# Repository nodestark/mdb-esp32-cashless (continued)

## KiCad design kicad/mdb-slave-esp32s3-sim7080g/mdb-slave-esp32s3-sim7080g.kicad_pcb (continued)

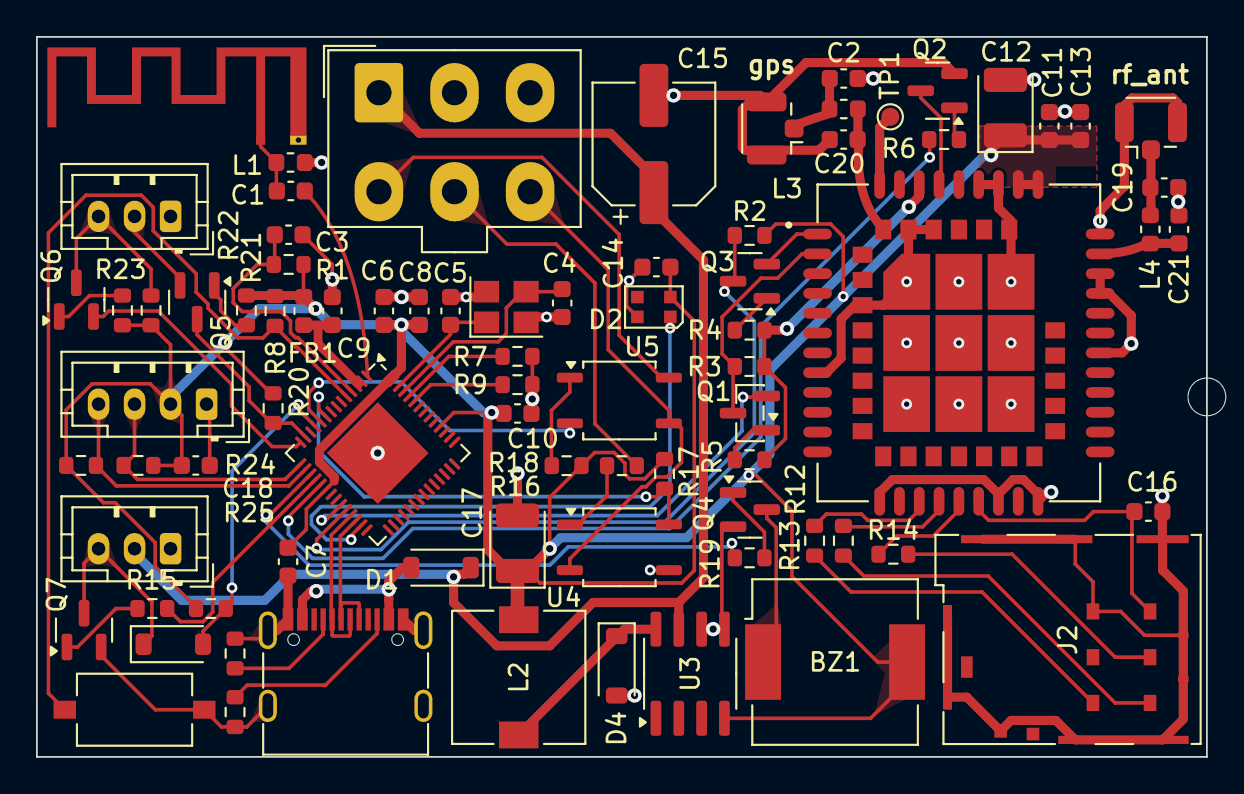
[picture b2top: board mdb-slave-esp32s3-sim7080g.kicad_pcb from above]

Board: 2 copper layers, 65.0 x 40.0 mm, 82 parts (0 on the bottom side), 63 nets.

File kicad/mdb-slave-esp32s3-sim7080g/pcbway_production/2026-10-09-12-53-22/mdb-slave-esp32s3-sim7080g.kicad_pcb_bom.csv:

Designator,Quantity,Value,Footprint,Package,MPN,DNP,Mount_Type,Description,LCSC#,MF,MAXIMUM_PACKAGE_HEIGHT,Price,Check_prices,STANDARD,PARTREV,SnapEDA_Link,MP,Description_1,Availability,MANUFACTURER
BZ1,1,Buzzer,Buzzer_CUI_CPT-9019S-SMT,,,,smt,"Buzzer, polarized",C255327,,,,,,,,,,,
"C1, C19, C2",3,1.8pf,C_0603_1608Metric,,,,smt,,C376773,,,,,,,,,,,
"C10, C11, C14, C16, C18, C7, C9",7,0.1uF,C_0603_1608Metric,,,,smt,,C5137636,,,,,,,,,,,
C12,1,10uF,CP_EIA-3528-21_Kemet-B,,,,smt,Polarized capacitor,C110053,,,,,,,,,,,
"C13, C3, C8",3,1uF,C_0603_1608Metric,,,,smt,,C6119849,,,,,,,,,,,
C15,1,100uF,CP_Elec_6.3x5.8,,,,smt,Polarized capacitor,C128464,,,,,,,,,,,
C17,1,220uF,CP_EIA-3528-21_Kemet-B,,,,smt,Polarized capacitor,C30242,,,,,,,,,,,
"C4, C5",2,12pF,C_0603_1608Metric,,,,smt,,C363546,,,,,,,,,,,
C6,1,10uF,C_0603_1608Metric,,,,smt,,C6119864,,,,,,,,,,,
"D1, D3, D4",3,D_Schottky,D_SOD-123,,,,smt,Schottky diode,C18195164,,,,,,,,,,,
D2,1,XL-2121RGBC-2812B,LED_WS2812B-2020_PLCC4_2.0x2.0mm,,,,smt,"RGB LED with integrated controller, 2.0 x 2.0 mm, 12 mA",C5349957,,,,,,,,,,,
FB1,1,FerriteBead_Small,L_0603_1608Metric,,,,smt,"Ferrite bead, small symbol",C14709,,,,,,,,,,,
J1,1,USB_C_Receptacle_USB2.0_16P,USB_C_Receptacle_G-Switch_GT-USB-7010ASV,,,,smt,USB 2.0-only 16P Type-C Receptacle connector,C2988369,,,,,,,,,,,
J2,1,JAE_SIM_Card_SF72S006,JAE_SIM_Card_SF72S006,,,,smt,Nano-SIM Card (4FF) connector with Detect Switch,C2977286,,,,,,,,,,,
"J3, J7",2,Conn_01x03_Pin,JST_PH_B3B-PH-K_1x03_P2.00mm_Vertical,,,,tht,"Generic connector, single row, 01x03, script generated",C131339,,,,,,,,,,,
"J4, J5",2,Conn_Coaxial,U.FL_Hirose_U.FL-R-SMT-1_Vertical,,,,smt,"coaxial connector (BNC, SMA, SMB, SMC, Cinch/RCA, LEMO, ...)",C88374,,,,,,,,,,,
J6,1,MDB_Connector,Molex_Mini-Fit_Jr_5566-06A_2x03_P4.20mm_Vertical,,,,tht,"Generic connector, double row, 02x03, top/bottom pin numbering scheme (row 1: 1...pins_per_row, row2: pins_per_row+1 ... num_pins), script generated (kicad-library-utils/schlib/autogen/connector/)",C22365701,,,,,,,,,,,
J8,1,Conn_01x04_Pin,JST_PH_B4B-PH-K_1x04_P2.00mm_Vertical,,,,tht,"Generic connector, single row, 01x04, script generated",C131334,,,,,,,,,,,
L1,1,2.4nh,L_0603_1608Metric,,,,smt,,C2042508,,,,,,,,,,,
L2,1,100uH,L_7.3x7.3_H3.5,,,,smt,Inductor,C182195,,,,,,,,,,,
L3,1,5.6nh,L_0603_1608Metric,,,,smt,,C6652920,,,,,,,,,,,
L4,1,3.9nh,L_0603_1608Metric,,,,smt,,C317982,,,,,,,,,,,
"Q1, Q2, Q3, Q4, Q5, Q6, Q7",7,MMBT3904,SOT-23,,,,smt,"0.2A Ic, 40V Vce, Small Signal NPN Transistor, SOT-23",C916374,,,,,,,,,,,
"R1, R2, R20, R22, R27, R3, R7, R8, R9",9,10k,R_0603_1608Metric,,,,smt,,C98220,,,,,,,,,,,
"R10, R11",2,5.1k,R_0603_1608Metric,,,,smt,,C394543,,,,,,,,,,,
"R12, R13, R14",3,22ohm,R_0603_1608Metric,,,,smt,,C23345,,,,,,,,,,,
"R15, R19, R21, R23, R24, R25, R4, R5, R6",9,4K7,R_0603_1608Metric,,,,smt,,C23162,,,,,,,,,,,
R16,1,470ohm,R_0603_1608Metric,,,,smt,Resistor,C114669,,,,,,,,,,,
R18,1,100ohm,R_0603_1608Metric,,,,smt,Resistor,C22775,,,,,,,,,,,
R17,1,1k,R_0603_1608Metric,,,,smt,,C2907113,,,,,,,,,,,
SW1,1,SW_Push,SW_Tactile_SPST_NO_Straight_CK_PTS636Sx25SMTRLFS,,,,smt,,C42435421,,,,,,,,,,,
U1,1,ESP32-S3FH4R2,QFN-56-1EP_7x7mm_P0.4mm_EP4x4mm,,,,smt,,C3013940,,,,,,,,,,,
U2,1,SIM7080G,XCVR_SIM7080G,Package,,,smt,,C2943992,SIMCom,2.6 mm,None,https://www.snapeda.com/parts/SIM7080G/SIMCom/view-part/?ref=eda,Manufacturer Recommendation,1.04,https://www.snapeda.com/parts/SIM7080G/SIMCom/view-part/?ref=snap,SIM7080G,"Cellular, Navigation Galileo, GLONASS, GPS, GNSS, LTE Transceiver Module 1.559GHz ~ 1.576GHz, 1.575GHz ~ 1.576GHz, 1.574GHz ~ 1.606GHz, 1.598GHz ~ 1.563GHz Antenna Not Included Surface Mount",In Stock,SIMCOM
U3,1,LM2594HVM-3.3,SOIC-8_3.9x4.9mm_P1.27mm,,,,smt,"3.3V, 0.5A SIMPLE SWITCHER® Step-Down Voltage Regulator, Maximum VIN 60V, SOIC-8",C18057294,,,,,,,,,,,
"U4, U5",2,TLP785,SOP-4_3.8x4.1mm_P2.54mm,,,,smt,"DC Optocoupler, Vce 80V, CTR 50-200%, DIP4",C128776,,,,,,,,,,,
Y1,1,Crystal_GND24,Crystal_SMD_3225-4Pin_3.2x2.5mm,,,,smt,"Four pin crystal, GND on pins 2 and 4",C7294599,,,,,,,,,,,

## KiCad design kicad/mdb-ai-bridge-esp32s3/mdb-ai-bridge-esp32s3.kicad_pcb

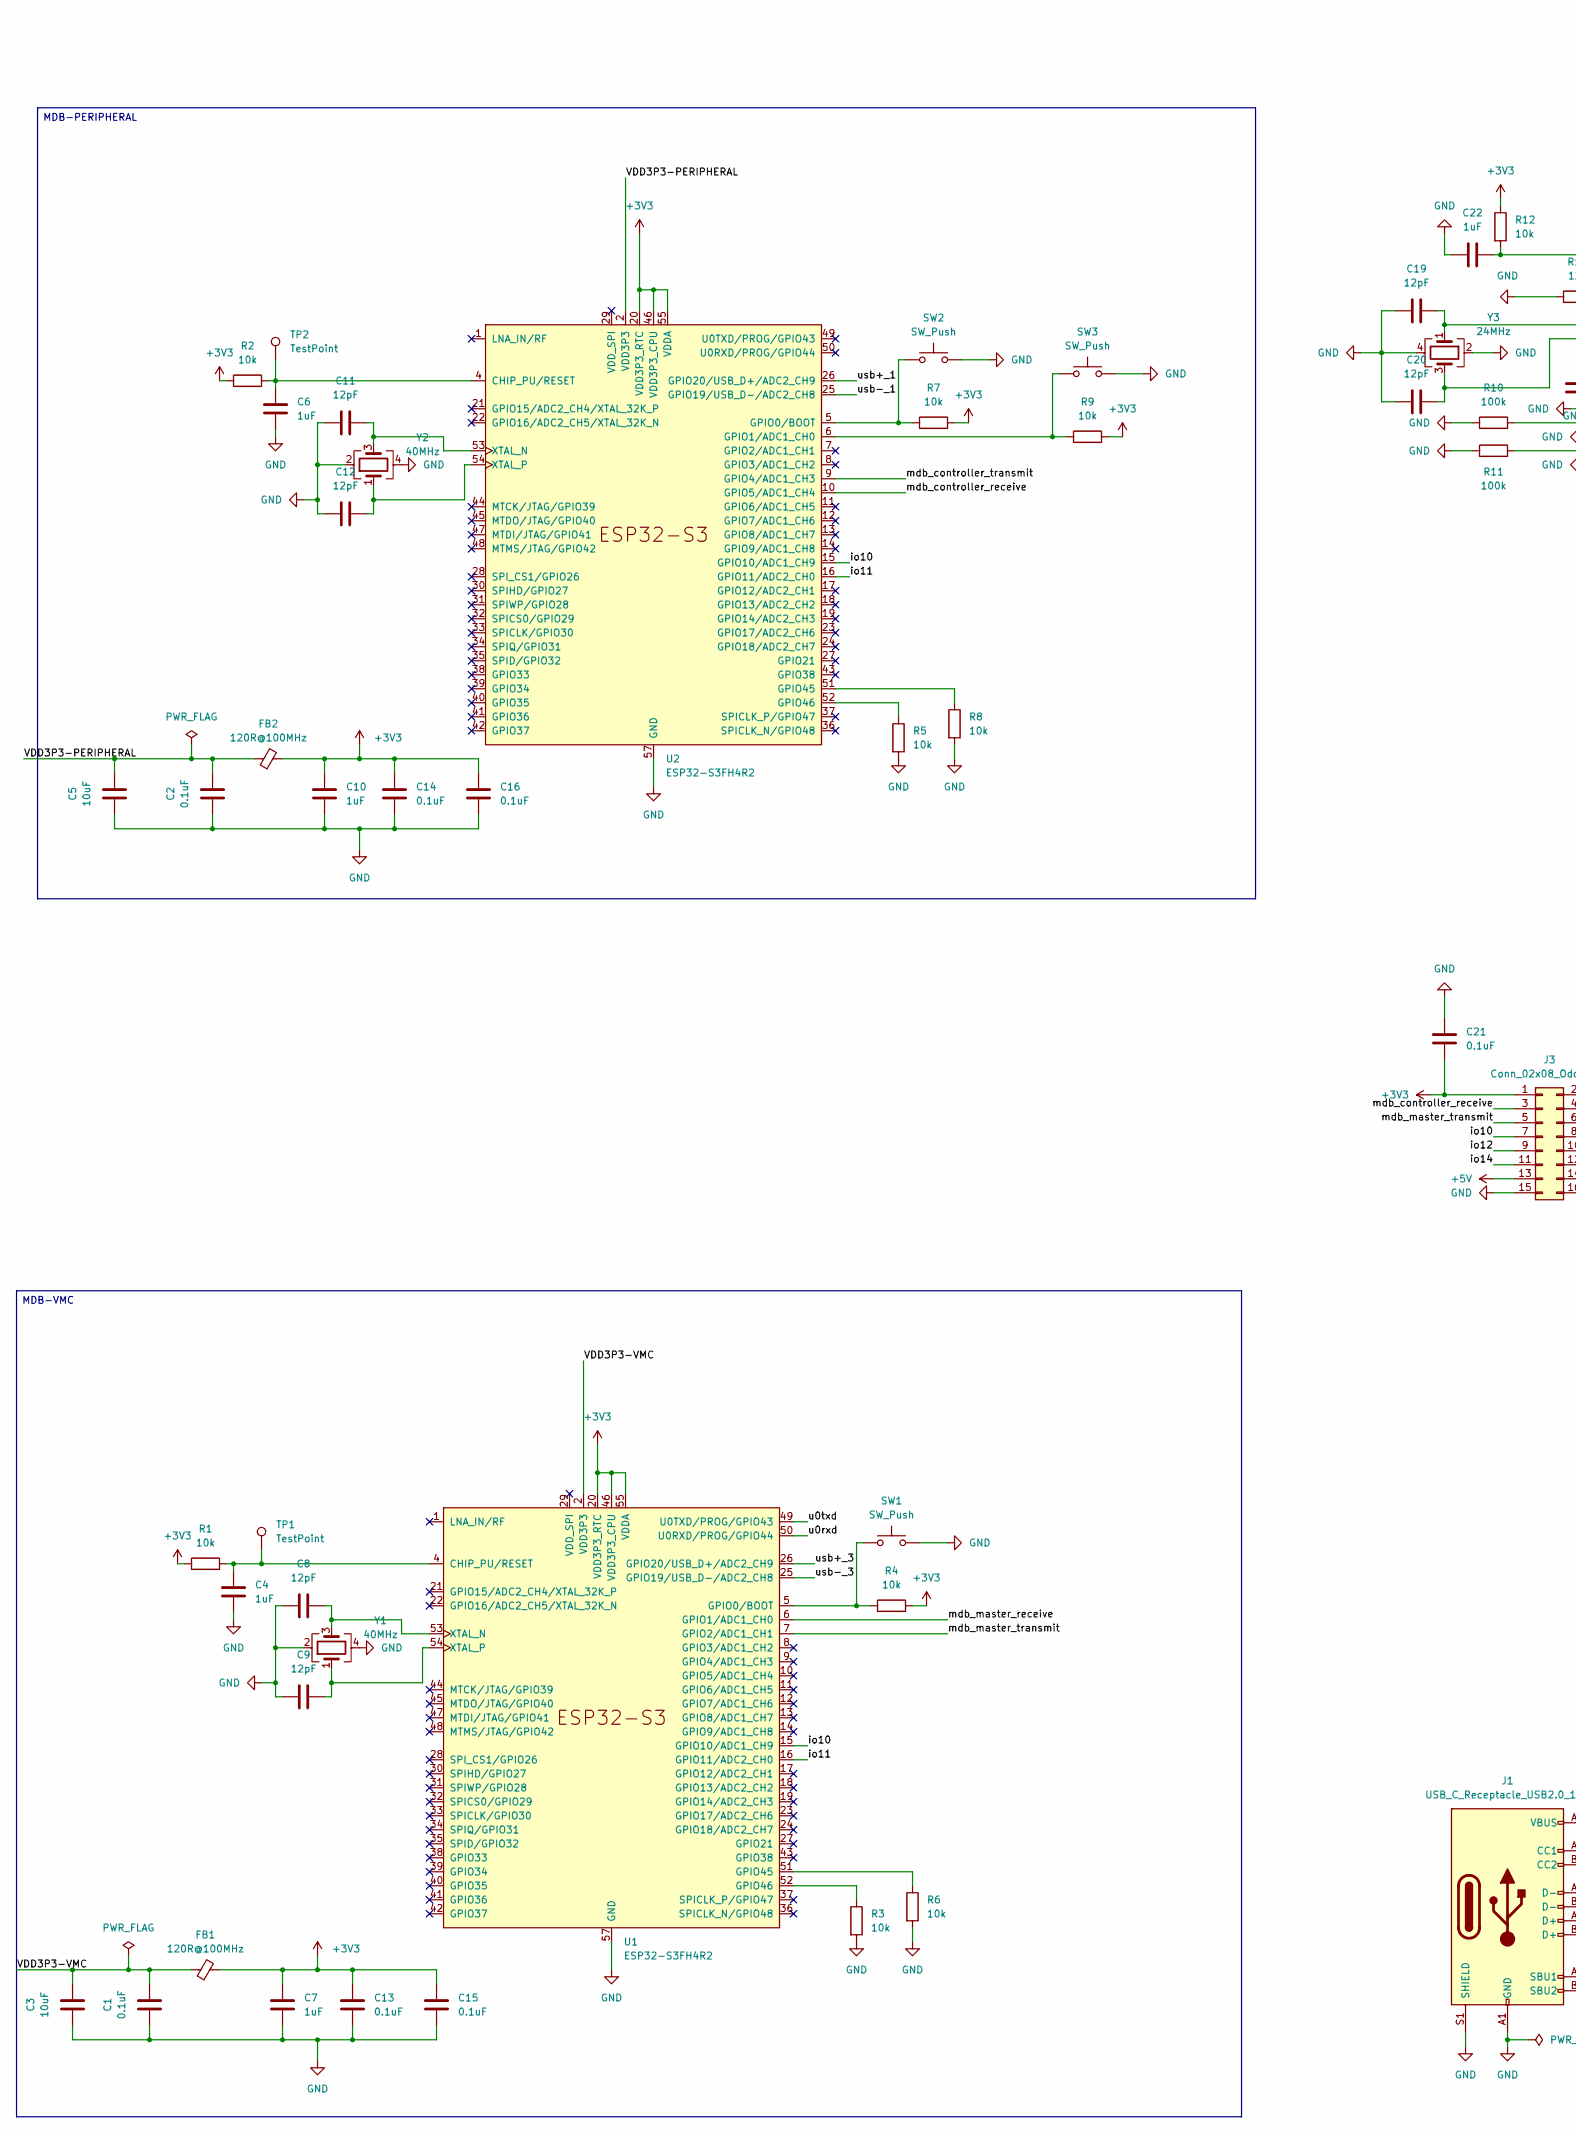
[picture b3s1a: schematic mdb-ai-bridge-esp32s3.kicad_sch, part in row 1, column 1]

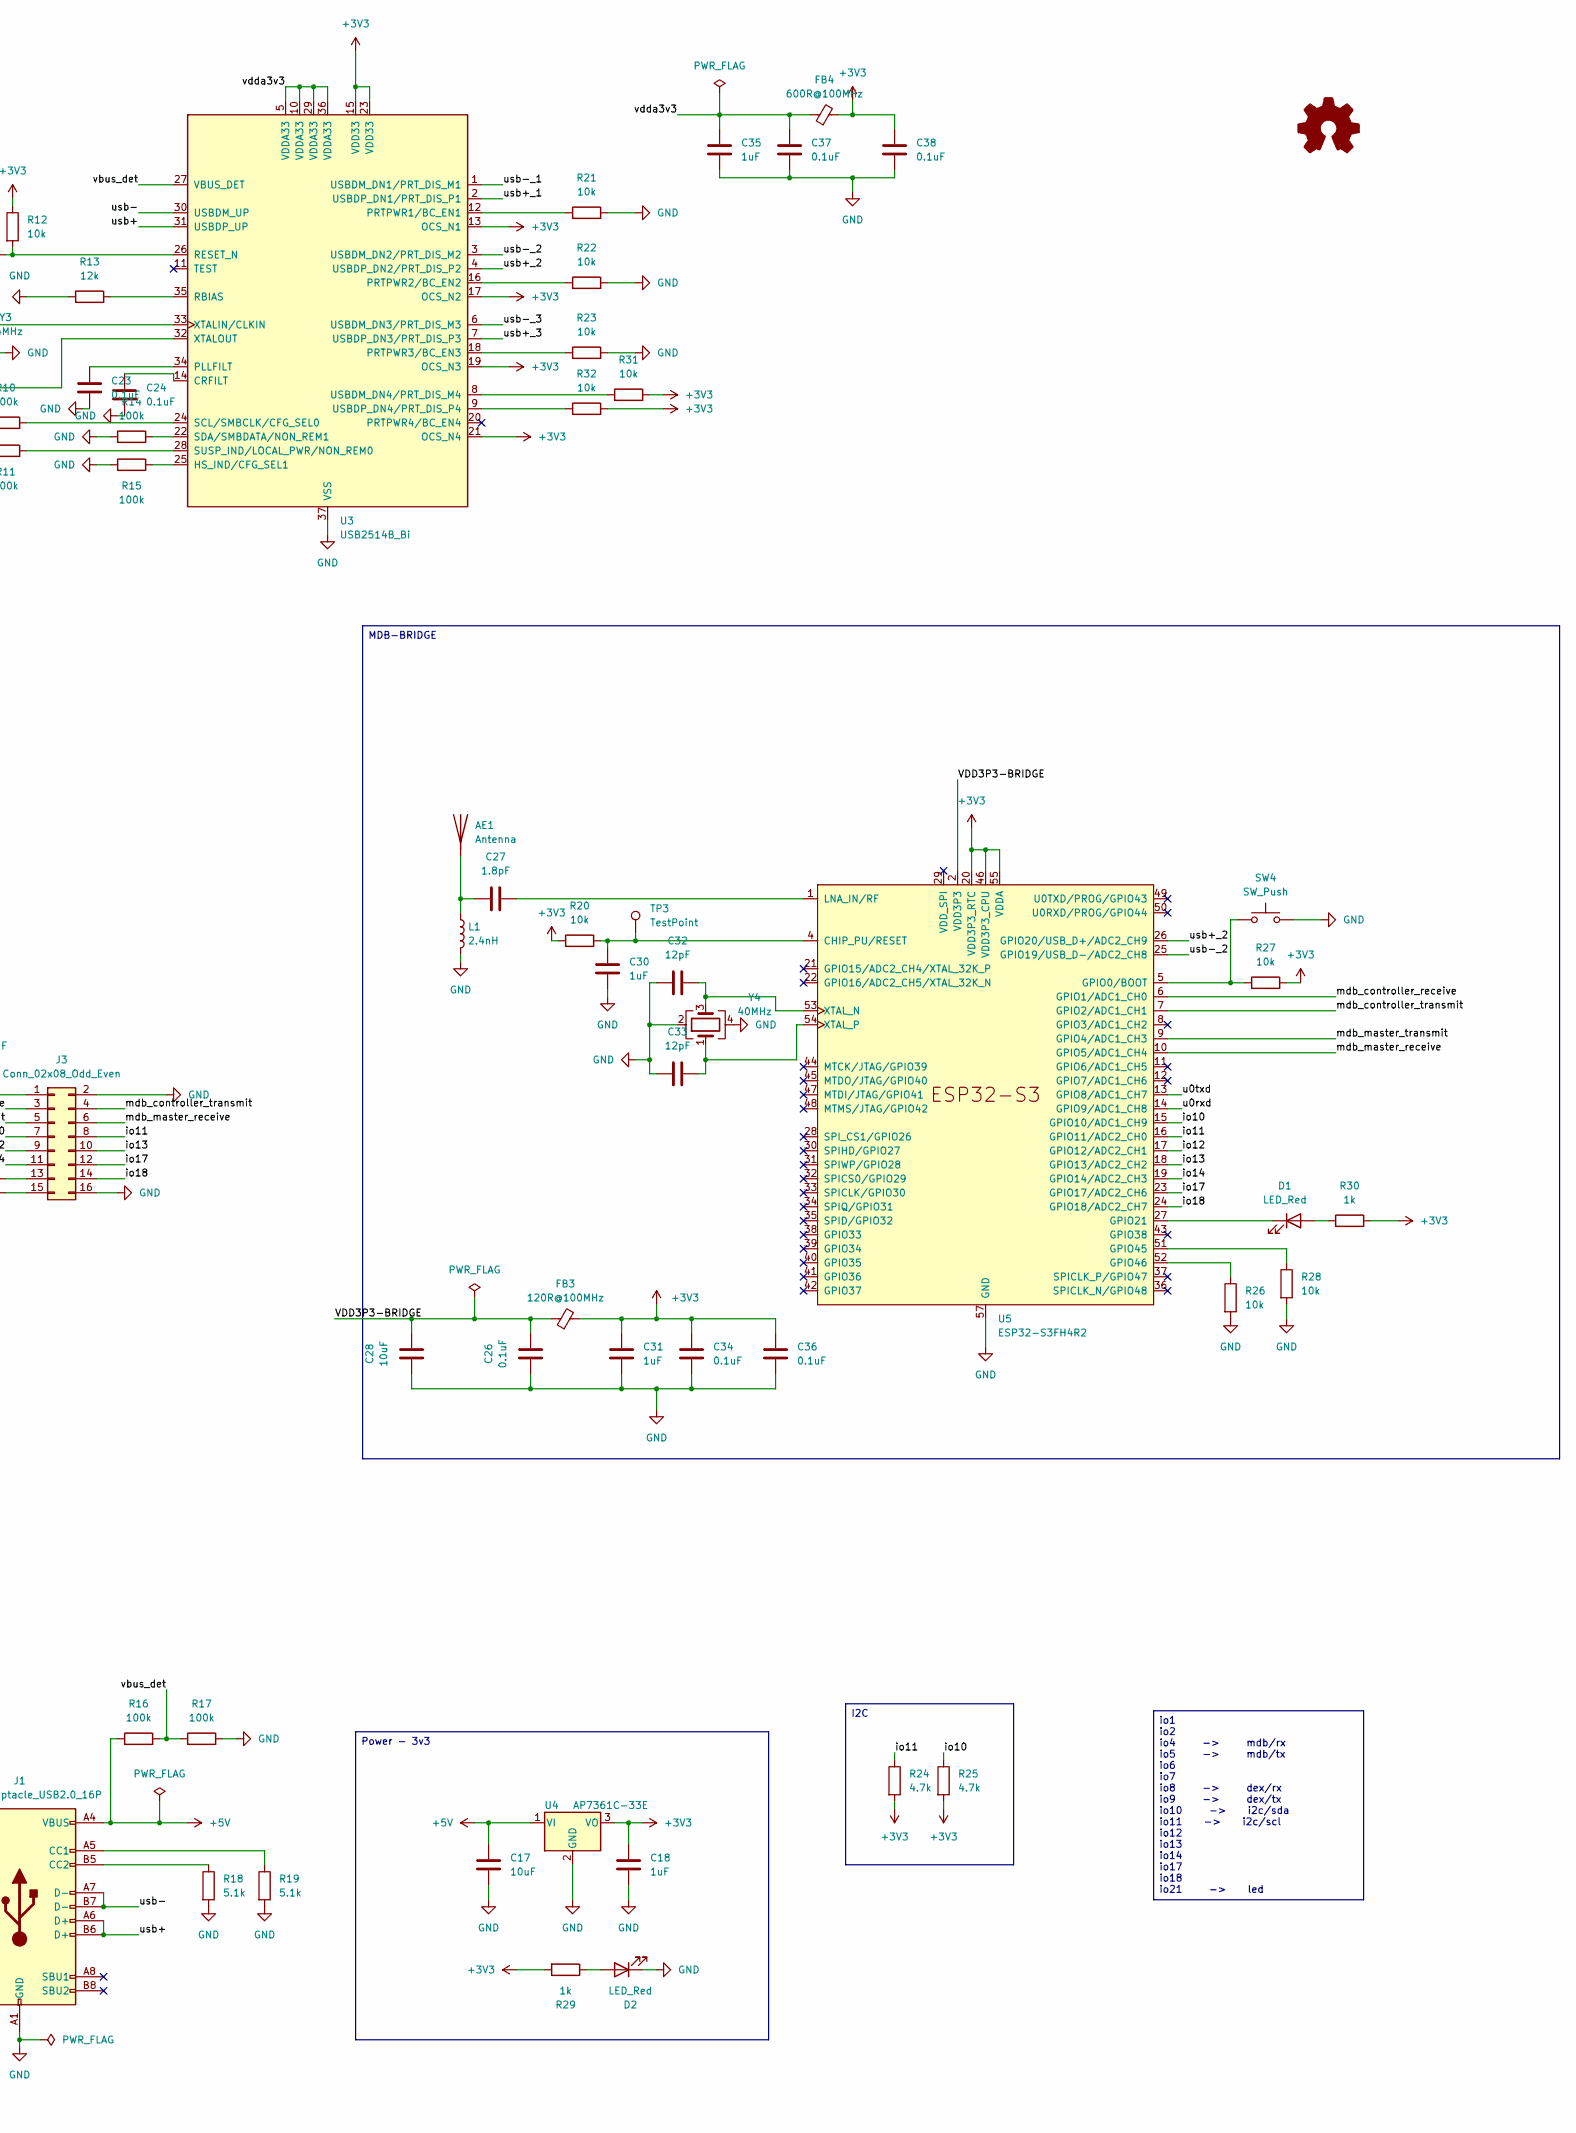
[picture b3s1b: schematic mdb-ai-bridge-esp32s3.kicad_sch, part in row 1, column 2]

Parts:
AE1: Antenna; Texas_SWRA117D_2.4GHz_Left
C1, C2, C13, C14, C15, C16, C21, C23, C24, C26, C34, C36, C37, C38: 0.1uF; C_0402_1005Metric; LCSC# C1525
C3, C5, C28: 10uF; C_0402_1005Metric; LCSC# C15525
C4, C6, C7, C10, C18, C22, C30, C31, C35: 1uF; C_0402_1005Metric; LCSC# C52923
C8, C9, C11, C12, C19, C20, C32, C33: 12pF; C_0402_1005Metric; LCSC# C1547
C17: 10uF; C_0402_1005Metric; LCSC# C7472949
C27: 1.8pF; C_0402_1005Metric; LCSC# C76902
D1, D2: LED_Red; LED_0402_1005Metric; LCSC# C779449
FB1, FB2, FB3: 120R@100MHz; L_0402_1005Metric; LCSC# C88970
FB4: 600R@100MHz; L_0402_1005Metric; LCSC# C160977
J1: USB_C_Receptacle_USB2.0_16P; USB_C_Receptacle_G-Switch_GT-USB-7010ASV; LCSC# C2988369
J3: Conn_02x08_Odd_Even; PinHeader_2x08_P2.54mm_Vertical
L1: 2.4nH; L_0402_1005Metric; LCSC# C167473
R1, R2, R3, R4, R5, R6, R7, R8, R9, R12, R20, R21, R22, R23, R26, R27, R28, R31, R32: 10k; R_0402_1005Metric; LCSC# C25744
R10, R11, R14, R15, R16, R17: 100k; R_0402_1005Metric; LCSC# C25741
R13: 12k; R_0402_1005Metric; LCSC# C25752
R18, R19: 5.1k; R_0402_1005Metric; LCSC# C25905
R24, R25: 4.7k; R_0402_1005Metric; LCSC# C25900
R29, R30: 1k; R_0402_1005Metric; LCSC# C11702
SW1, SW2, SW3, SW4: SW_Push; SW_Tactile_SPST_NO_Straight_CK_PTS636Sx25SMTRLFS; LCSC# C42435421
TP1, TP2, TP3: TestPoint; TestPoint_Pad_D1.5mm
U1, U2, U5: ESP32-S3FH4R2; QFN-56-1EP_7x7mm_P0.4mm_EP4x4mm; LCSC# C3013940
U3: USB2514B_Bi; QFN-36-1EP_6x6mm_P0.5mm_EP3.7x3.7mm; LCSC# C510949
U4: AP7361C-33E; SOT-223-3_TabPin2; LCSC# C500795
Y1, Y2, Y4: 40MHz; Crystal_SMD_3225-4Pin_3.2x2.5mm; LCSC# C7294599
Y3: 24MHz; Crystal_SMD_3225-4Pin_3.2x2.5mm; LCSC# C70583

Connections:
+3V3: C7.2, C10.2, C13.1, C14.1, C15.1, C16.1, C18.2, C21.1, C31.2, C34.1, C36.1, C38.1, FB1.2, FB2.2, FB3.2, FB4.2, J3.1, R1.1, R2.1, R4.2, R7.2, R9.2, R12.1, R20.1, R24.2, R25.2, R27.2, R29.2, R30.2, R31.2, R32.2, U1.20 (VDD3P3_RTC), U1.46 (VDD3P3_CPU), U1.55 (VDDA), U1.56 (VDDA), U2.20 (VDD3P3_RTC), U2.46 (VDD3P3_CPU), U2.55 (VDDA), U2.56 (VDDA), U3.13 (OCS_N1), U3.15 (VDD33), U3.17 (OCS_N2), U3.19 (OCS_N3), U3.21 (OCS_N4), U3.23 (VDD33), U4.3 (VO), U5.20 (VDD3P3_RTC), U5.46 (VDD3P3_CPU), U5.55 (VDDA), U5.56 (VDDA)
+5V: C17.2, J1.A4 (VBUS), J1.A9 (VBUS), J1.B4 (VBUS), J1.B9 (VBUS), J3.13, R16.1, U4.1 (VI)
/VDD3P3-BRIDGE: C26.2, C28.2, FB3.1, U5.2 (VDD3P3), U5.3 (VDD3P3)
/VDD3P3-PERIPHERAL: C2.2, C5.2, FB2.1, U2.2 (VDD3P3), U2.3 (VDD3P3)
/VDD3P3-VMC: C1.2, C3.2, FB1.1, U1.2 (VDD3P3), U1.3 (VDD3P3)
/io10: J3.7, R25.1, U1.15 (GPIO10/ADC1_CH9), U2.15 (GPIO10/ADC1_CH9), U5.15 (GPIO10/ADC1_CH9)
/io11: J3.8, R24.1, U1.16 (GPIO11/ADC2_CH0), U2.16 (GPIO11/ADC2_CH0), U5.16 (GPIO11/ADC2_CH0)
/io12: J3.9, U5.17 (GPIO12/ADC2_CH1)
/io13: J3.10, U5.18 (GPIO13/ADC2_CH2)
/io14: J3.11, U5.19 (GPIO14/ADC2_CH3)
/io17: J3.12, U5.23 (GPIO17/ADC2_CH6)
/io18: J3.14, U5.24 (GPIO18/ADC2_CH7)
/mdb_controller_receive: J3.3, U2.10 (GPIO5/ADC1_CH4), U5.6 (GPIO1/ADC1_CH0)
/mdb_controller_transmit: J3.4, U2.9 (GPIO4/ADC1_CH3), U5.7 (GPIO2/ADC1_CH1)
/mdb_master_receive: J3.6, U1.6 (GPIO1/ADC1_CH0), U5.10 (GPIO5/ADC1_CH4)
/mdb_master_transmit: J3.5, U1.7 (GPIO2/ADC1_CH1), U5.9 (GPIO4/ADC1_CH3)
/u0rxd: U1.50 (U0RXD/PROG/GPIO44), U5.14 (GPIO9/ADC1_CH8)
/u0txd: U1.49 (U0TXD/PROG/GPIO43), U5.13 (GPIO8/ADC1_CH7)
/usb+: J1.A6 (D+), J1.B6 (D+), U3.31 (USBDP_UP)
/usb+_1: U2.26 (GPIO20/USB_D+/ADC2_CH9), U3.2 (USBDP_DN1/PRT_DIS_P1)
/usb+_2: U3.4 (USBDP_DN2/PRT_DIS_P2), U5.26 (GPIO20/USB_D+/ADC2_CH9)
/usb+_3: U1.26 (GPIO20/USB_D+/ADC2_CH9), U3.7 (USBDP_DN3/PRT_DIS_P3)
/usb-: J1.A7 (D-), J1.B7 (D-), U3.30 (USBDM_UP)
/usb-_1: U2.25 (GPIO19/USB_D-/ADC2_CH8), U3.1 (USBDM_DN1/PRT_DIS_M1)
/usb-_2: U3.3 (USBDM_DN2/PRT_DIS_M2), U5.25 (GPIO19/USB_D-/ADC2_CH8)
/usb-_3: U1.25 (GPIO19/USB_D-/ADC2_CH8), U3.6 (USBDM_DN3/PRT_DIS_M3)
/vbus_det: R16.2, R17.1, U3.27 (VBUS_DET)
/vdda3v3: C35.2, C37.1, FB4.1, U3.5 (VDDA33), U3.10 (VDDA33), U3.29 (VDDA33), U3.36 (VDDA33)
GND: C1.1, C2.1, C3.1, C4.2, C5.1, C6.2, C7.1, C8.1, C9.1, C10.1, C11.1, C12.1, C13.2, C14.2, C15.2, C16.2, C17.1, C18.1, C19.1, C20.1, C21.2, C22.2, C23.1, C24.1, C26.1, C28.1, C30.2, C31.1, C32.1, C33.1, C34.2, C35.1, C36.2, C37.2, C38.2, D2.1 (K), J1.A1 (GND), J1.A12 (GND), J1.B1 (GND), J1.B12 (GND), J1.S1 (SHIELD), J3.2, J3.15, J3.16, L1.2, R3.2, R5.2, R6.2, R8.2, R10.1, R11.1, R13.1, R14.1, R15.1, R17.2, R18.2, R19.2, R21.2, R22.2, R23.2, R26.2, R28.2, SW1.2, SW2.2, SW3.2, SW4.2, U1.57 (GND), U2.57 (GND), U3.37 (VSS), U4.2 (GND), U5.57 (GND), Y1.2, Y1.4, Y2.2, Y2.4, Y3.2, Y3.4, Y4.2, Y4.4
unnamed: AE1.1 (A), C27.1, L1.1
unnamed: D1.2 (A), R30.1
unnamed: D1.1 (K), U5.27 (GPIO21)
unnamed: D2.2 (A), R29.1
unnamed: J1.A5 (CC1), R19.1
unnamed: J1.B5 (CC2), R18.1
unnamed: C4.1, R1.2, TP1.1, U1.4 (CHIP_PU/RESET)
unnamed: R4.1, SW1.1, U1.5 (GPIO0/BOOT)
unnamed: R6.1, U1.51 (GPIO45)
unnamed: R3.1, U1.52 (GPIO46)
unnamed: C8.2, U1.53 (XTAL_N), Y1.3
unnamed: C9.2, U1.54 (XTAL_P), Y1.1
unnamed: C6.1, R2.2, TP2.1, U2.4 (CHIP_PU/RESET)
unnamed: R7.1, SW2.1, U2.5 (GPIO0/BOOT)
unnamed: R9.1, SW3.1, U2.6 (GPIO1/ADC1_CH0)
unnamed: R8.1, U2.51 (GPIO45)
unnamed: R5.1, U2.52 (GPIO46)
unnamed: C11.2, U2.53 (XTAL_N), Y2.3
unnamed: C12.2, U2.54 (XTAL_P), Y2.1
unnamed: C24.2, U3.14 (CRFILT)
unnamed: R15.2, U3.25 (HS_IND/CFG_SEL1)
unnamed: C23.2, U3.34 (PLLFILT)
unnamed: R21.1, U3.12 (PRTPWR1/BC_EN1)
unnamed: R22.1, U3.16 (PRTPWR2/BC_EN2)
unnamed: R23.1, U3.18 (PRTPWR3/BC_EN3)
unnamed: R13.2, U3.35 (RBIAS)
unnamed: C22.1, R12.2, U3.26 (RESET_N)
unnamed: R10.2, U3.24 (SCL/SMBCLK/CFG_SEL0)
unnamed: R14.2, U3.22 (SDA/SMBDATA/NON_REM1)
unnamed: R11.2, U3.28 (SUSP_IND/LOCAL_PWR/NON_REM0)
unnamed: R31.1, U3.8 (USBDM_DN4/PRT_DIS_M4)
unnamed: R32.1, U3.9 (USBDP_DN4/PRT_DIS_P4)
unnamed: C19.2, U3.33 (XTALIN/CLKIN), Y3.1
unnamed: C20.2, U3.32 (XTALOUT), Y3.3
unnamed: C30.1, R20.2, TP3.1, U5.4 (CHIP_PU/RESET)
unnamed: R27.1, SW4.1, U5.5 (GPIO0/BOOT)
unnamed: R28.1, U5.51 (GPIO45)
unnamed: R26.1, U5.52 (GPIO46)
unnamed: C27.2, U5.1 (LNA_IN/RF)
unnamed: C32.2, U5.53 (XTAL_N), Y4.3
unnamed: C33.2, U5.54 (XTAL_P), Y4.1

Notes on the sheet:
MDB-PERIPHERAL
Power - 3v3
MDB-BRIDGE
MDB-VMC
io1 io2 io4 -> mdb/rx io5 -> mdb/tx io6 io7 io8 -> dex/rx io9 -> dex/tx io10 -> i2c/sda io11 -> i2c/scl io12 io13 io14 io17 io18 io21 -> led
I2C

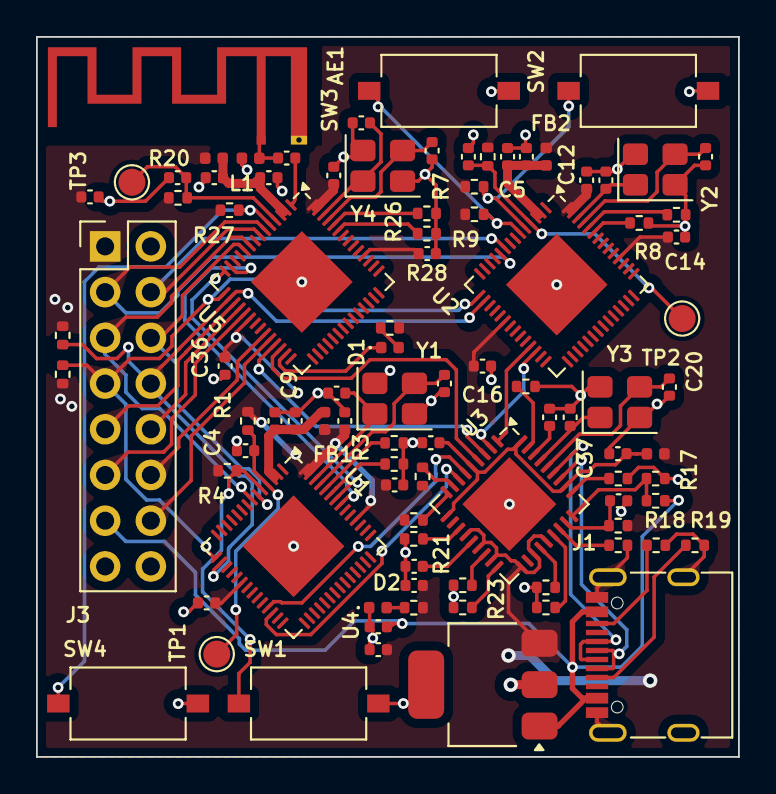
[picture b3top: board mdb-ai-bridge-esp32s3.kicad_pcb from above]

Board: 2 copper layers, 39.0 x 40.0 mm, 94 parts (0 on the bottom side), 70 nets.

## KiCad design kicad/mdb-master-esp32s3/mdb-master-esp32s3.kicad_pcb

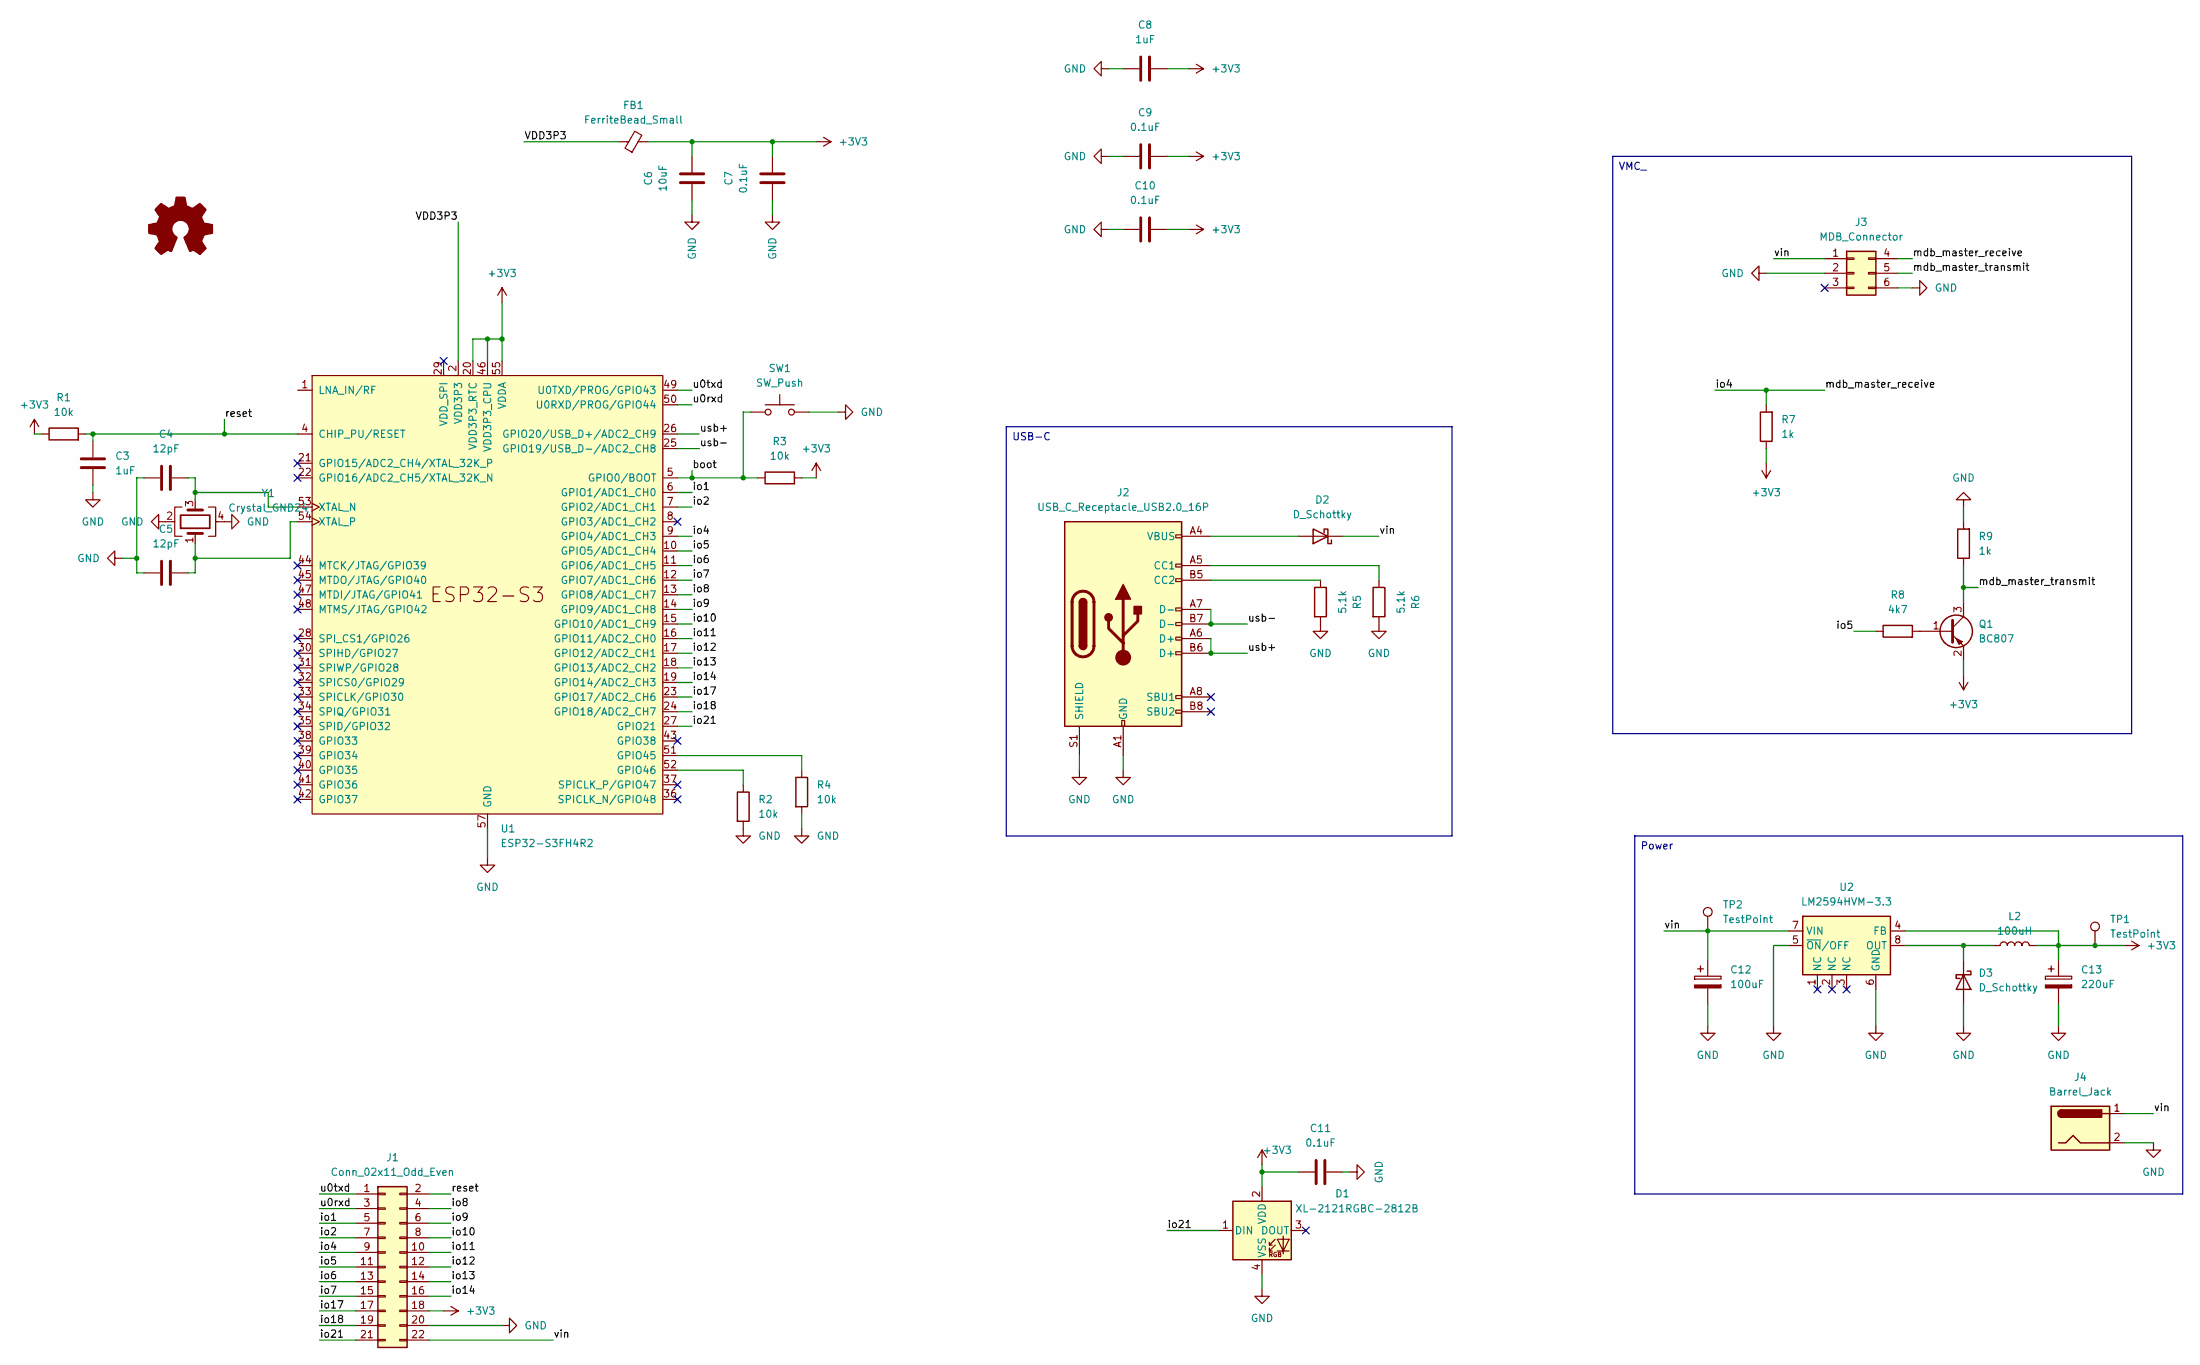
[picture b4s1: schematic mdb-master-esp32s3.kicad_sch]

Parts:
C3, C8: 1uF; C_0603_1608Metric; LCSC# C6119849
C4, C5: 12pF; C_0603_1608Metric; LCSC# C363546
C6: 10uF; C_0603_1608Metric; LCSC# C6119864
C7, C9, C10, C11: 0.1uF; C_0603_1608Metric; LCSC# C5137636
C12: 100uF; CP_Elec_6.3x5.8; LCSC# C128464
C13: 220uF; CP_EIA-3528-21_Kemet-B; LCSC# C30242
D1: XL-2121RGBC-2812B; LED_WS2812B-2020_PLCC4_2.0x2.0mm; LCSC# C5349957
D2, D3: D_Schottky; D_SOD-123; LCSC# C18195164
FB1: FerriteBead_Small; L_0603_1608Metric; LCSC# C304319
J1: Conn_02x11_Odd_Even; PinHeader_2x11_P2.54mm_Vertical; LCSC# C41375952
J2: USB_C_Receptacle_USB2.0_16P; USB_C_Receptacle_G-Switch_GT-USB-7010ASV; LCSC# C2988369
J3: MDB_Connector; Molex_Mini-Fit_Jr_5566-06A_2x03_P4.20mm_Vertical; LCSC# C22365701
J4: Barrel_Jack; BarrelJack_Horizontal; LCSC# C7498153
L2: 100uH; L_7.3x7.3_H3.5; LCSC# C182195
Q1: BC807; SOT-23; LCSC# C57316
R1, R2, R3, R4: 10k; R_0603_1608Metric; LCSC# C98220
R5, R6: 5.1k; R_0603_1608Metric; LCSC# C394543
R7, R9: 1k; R_0603_1608Metric; LCSC# C2907113
R8: 4k7; R_0603_1608Metric; LCSC# C23162
SW1: SW_Push; SW_Tactile_SPST_NO_Straight_CK_PTS636Sx25SMTRLFS; LCSC# C42435421
TP1, TP2: TestPoint; TestPoint_Pad_D1.0mm
U1: ESP32-S3FH4R2; QFN-56-1EP_7x7mm_P0.4mm_EP4x4mm; LCSC# C3013940
U2: LM2594HVM-3.3; SOIC-8_3.9x4.9mm_P1.27mm; LCSC# C18057294
Y1: Crystal_GND24; Crystal_SMD_3225-4Pin_3.2x2.5mm; LCSC# C7294599

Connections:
+3V3: C6.2, C7.2, C8.2, C9.2, C10.2, C11.2, C13.1, D1.2 (VDD), FB1.2, J1.18, L2.2, Q1.2 (E), R1.1, R3.2, R7.1, TP1.1, U1.20 (VDD3P3_RTC), U1.46 (VDD3P3_CPU), U1.55 (VDDA), U1.56 (VDDA), U2.4 (FB)
/boot: R3.1, SW1.1, U1.5 (GPIO0/BOOT)
/io1: J1.5, U1.6 (GPIO1/ADC1_CH0)
/io2: J1.7, U1.7 (GPIO2/ADC1_CH1)
/io4: J1.9, J3.4, R7.2, U1.9 (GPIO4/ADC1_CH3)
/io5: J1.11, R8.1, U1.10 (GPIO5/ADC1_CH4)
/io6: J1.13, U1.11 (GPIO6/ADC1_CH5)
/io7: J1.15, U1.12 (GPIO7/ADC1_CH6)
/io8: J1.4, U1.13 (GPIO8/ADC1_CH7)
/io9: J1.6, U1.14 (GPIO9/ADC1_CH8)
/io10: J1.8, U1.15 (GPIO10/ADC1_CH9)
/io11: J1.10, U1.16 (GPIO11/ADC2_CH0)
/io12: J1.12, U1.17 (GPIO12/ADC2_CH1)
/io13: J1.14, U1.18 (GPIO13/ADC2_CH2)
/io14: J1.16, U1.19 (GPIO14/ADC2_CH3)
/io17: J1.17, U1.23 (GPIO17/ADC2_CH6)
/io18: J1.19, U1.24 (GPIO18/ADC2_CH7)
/io21: D1.1 (DIN), J1.21, U1.27 (GPIO21)
/mdb_master_transmit: J3.5, Q1.3 (C), R9.1
/reset: C3.1, J1.2, R1.2, U1.4 (CHIP_PU/RESET)
/u0rxd: J1.3, U1.50 (U0RXD/PROG/GPIO44)
/u0txd: J1.1, U1.49 (U0TXD/PROG/GPIO43)
/usb+: J2.A6 (D+), J2.B6 (D+), U1.26 (GPIO20/USB_D+/ADC2_CH9)
/usb-: J2.A7 (D-), J2.B7 (D-), U1.25 (GPIO19/USB_D-/ADC2_CH8)
/vin: C12.1, D2.1 (K), J1.22, J3.1, J4.1, TP2.1, U2.7 (VIN)
GND: C3.2, C4.1, C5.1, C6.1, C7.1, C8.1, C9.1, C10.1, C11.1, C12.2, C13.2, D1.4 (VSS), D3.2 (A), J1.20, J2.A1 (GND), J2.A12 (GND), J2.B1 (GND), J2.B12 (GND), J2.S1 (SHIELD), J3.2, J3.6, J4.2, R2.2, R4.2, R5.2, R6.2, R9.2, SW1.2, U1.57 (GND), U2.5 (~ON/OFF), U2.6 (GND), Y1.2, Y1.4
unnamed: D2.2 (A), J2.A4 (VBUS), J2.A9 (VBUS), J2.B4 (VBUS), J2.B9 (VBUS)
unnamed: D3.1 (K), L2.1, U2.8 (OUT)
unnamed: J2.A5 (CC1), R6.1
unnamed: J2.B5 (CC2), R5.1
unnamed: Q1.1 (B), R8.2
unnamed: R4.1, U1.51 (GPIO45)
unnamed: R2.1, U1.52 (GPIO46)
unnamed: C4.2, U1.53 (XTAL_N), Y1.3
unnamed: C5.2, U1.54 (XTAL_P), Y1.1
VDD3P3: FB1.1, U1.2 (VDD3P3), U1.3 (VDD3P3)

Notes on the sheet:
Power
VMC_
USB-C

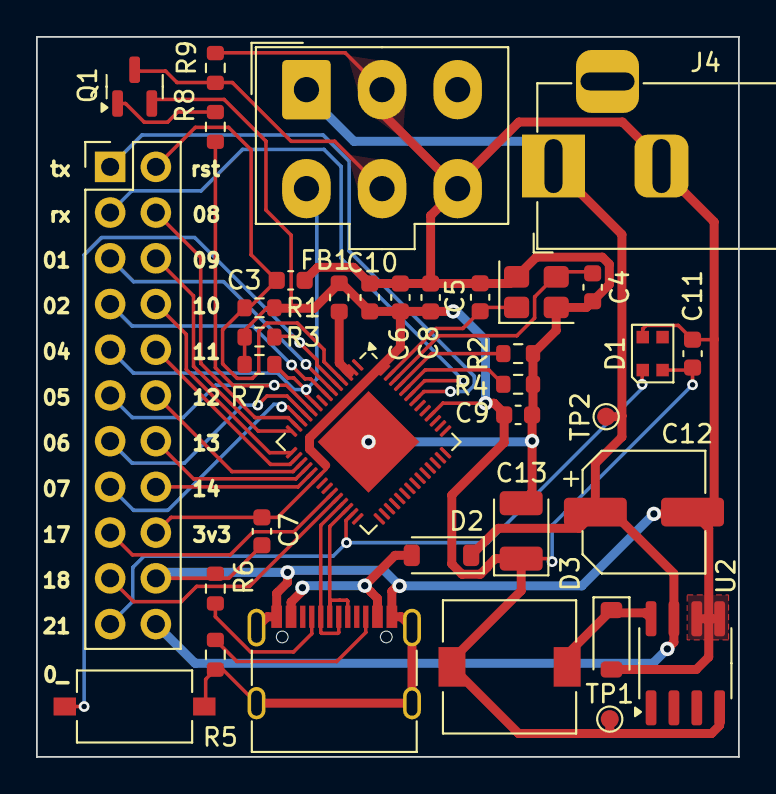
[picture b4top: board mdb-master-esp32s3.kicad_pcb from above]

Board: 2 copper layers, 39.0 x 40.0 mm, 36 parts (0 on the bottom side), 36 nets.
